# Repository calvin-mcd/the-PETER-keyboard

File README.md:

# the PETER keyboard

compact 60ish keyboard inspired by 40s layouts & formfactors

I designed this keyboard after asking my friend Peter what his ideal keyboard would be. His answer was:"Ehm... I like numbers!". So I tried to make a board that keeps the functionality of a 60% keyboard while offering it in a 40s inspired form factor.

It takes inspiration from ai03’s [UT47.2](https://github.com/ai03-2725/UT47.2) and EODesigns\#4352’s [Humble40](https://geekhack.org/index.php?topic=112927.0) as well as trash man\#6005’s [v4n4g0n](https://trashman.wiki/keyboards/v4n4g0n) and NoahK\#1290’s [Monorail](https://trashman.wiki/community/pcbs/monorail) pcbs.

The case is based on rain\#3950's [mfr2](https://github.com/rainkeebs/mfr2) and has been edited by Gizzle\#9369 to allow for bottom mounting inspired by projectcain\#5265's [vault35](https://mechvault.net/products/vault-35-mini-keyboard)

## Layout

[Link](https://www.keyboard-layout-editor.com/#/gists/bfbfb0e68d74f1cbb328a13727df050d)

## Pictures

## Disclaimer

This project has been tested and confirmed to work. However, no-one involved in this project is responsible for any usage issues that may arise. Order at your own risk. Feel free to edit, modify and otherwise utilise these files.

## License

This project is released under the GPL v3 License. Please refer to the LICENCE file.

## Credits

As always big thanks to the many people who helped me with the pcb, firmware, case design and much more! Escpecially NoahK\#1290, Gizzle\#9369, Iceage\#8817, Dana\#5035, Sierry\#7140 & TweetyDaBird\#3276!

Any questions, contact Calvin\#0563 on Discord.

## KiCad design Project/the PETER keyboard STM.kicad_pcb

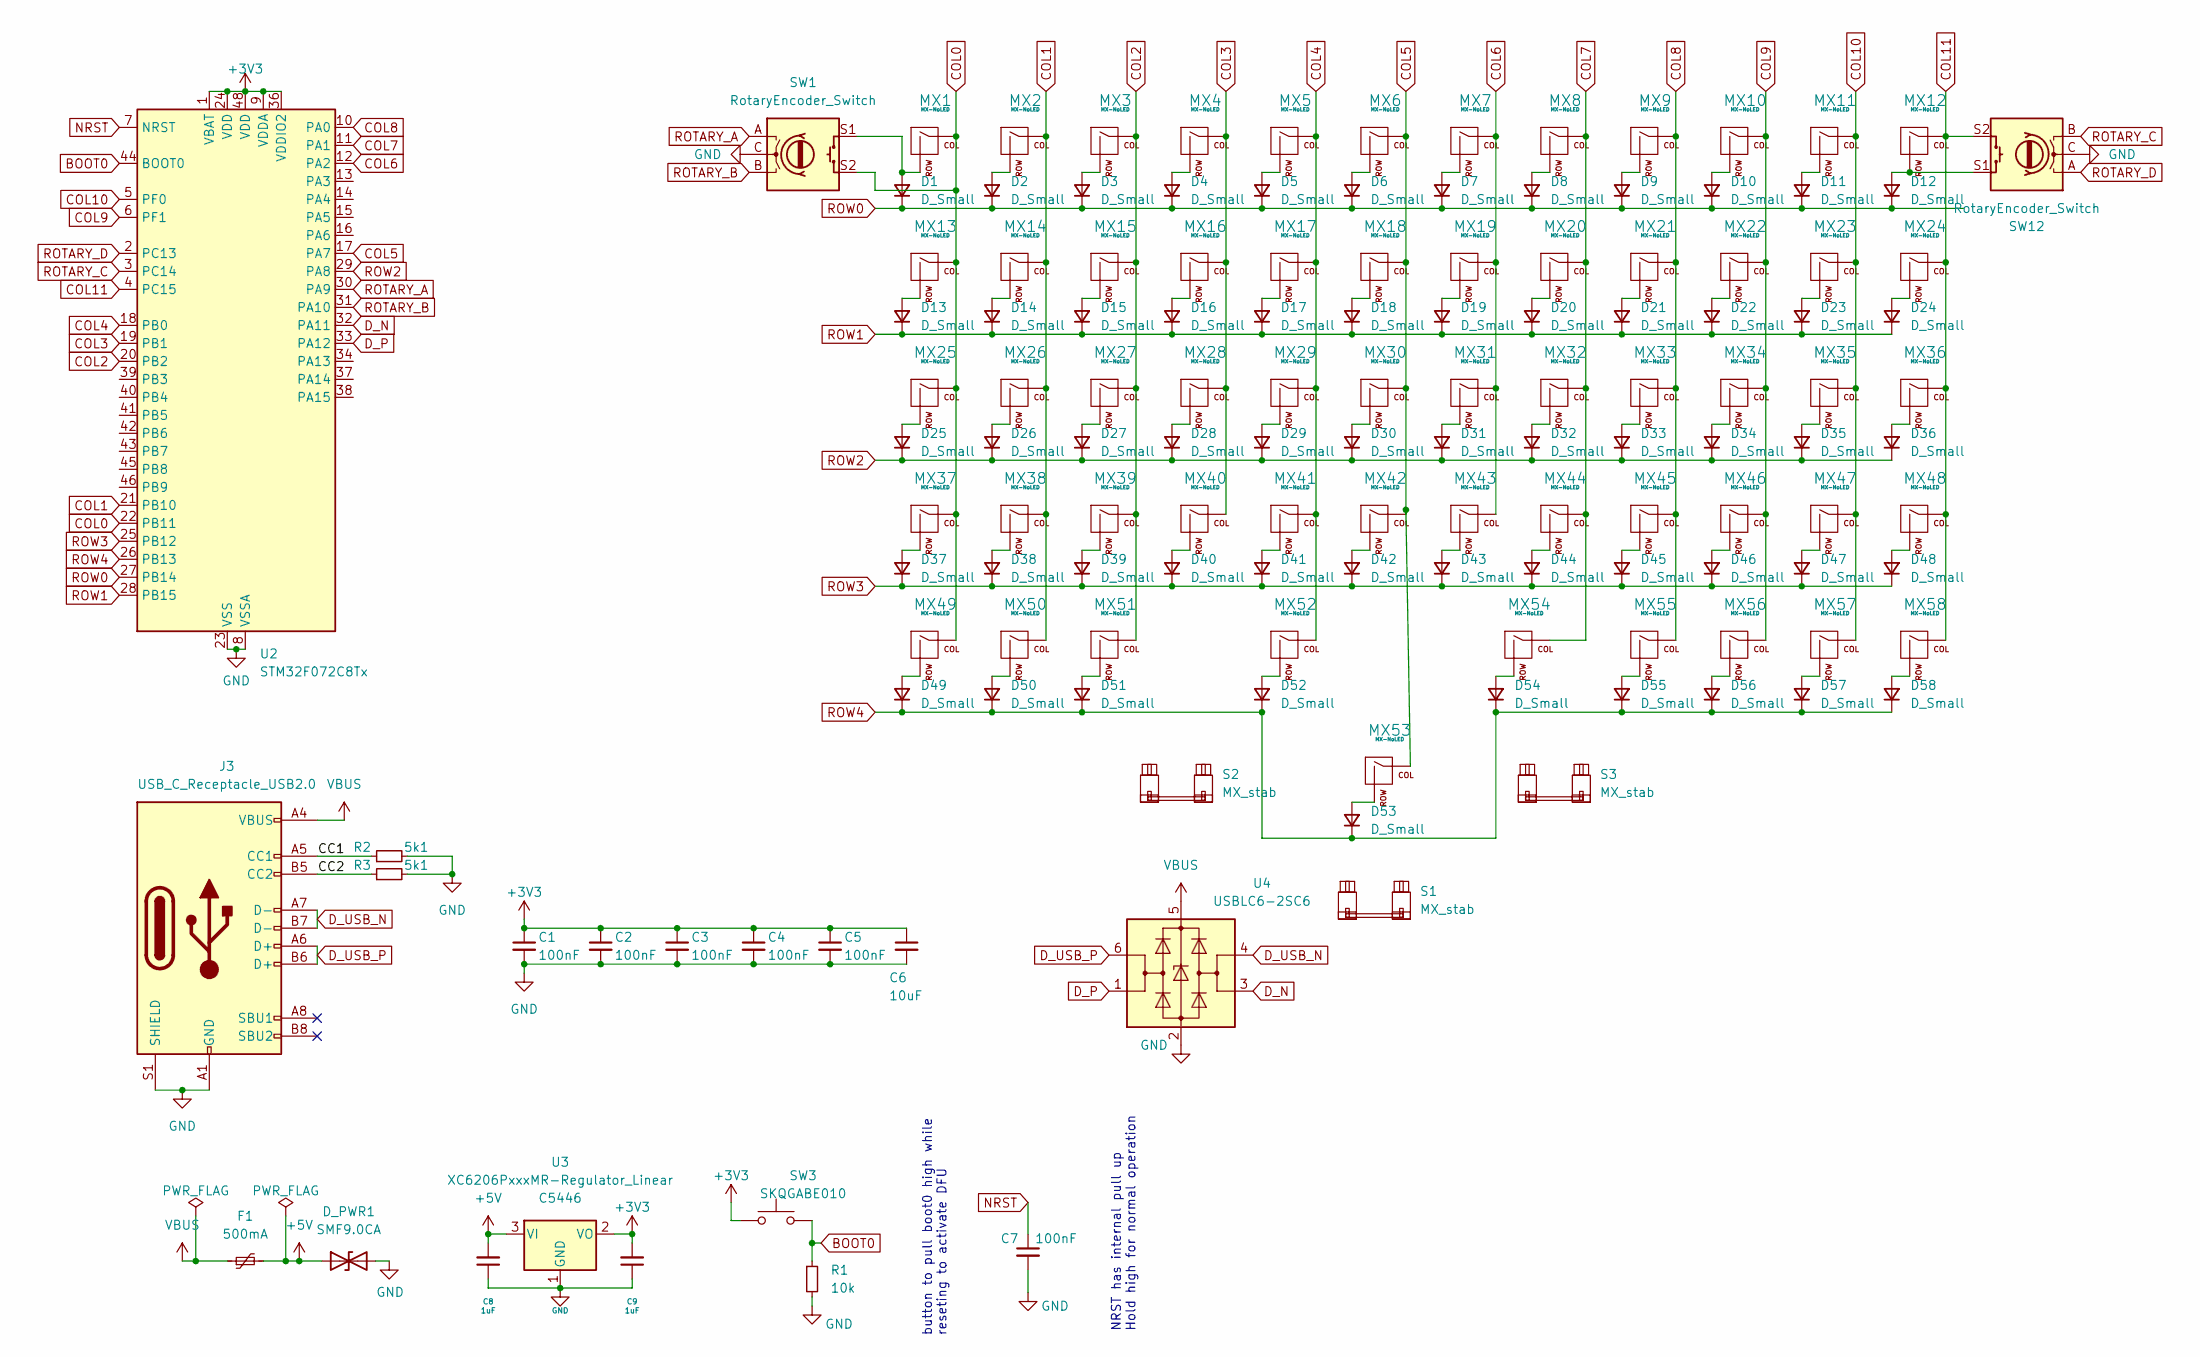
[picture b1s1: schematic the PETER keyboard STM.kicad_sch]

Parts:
C1, C2, C3, C4, C5: 100nF; C_0402_1005Metric
C6: 10uF; C_0402_1005Metric
C7: 100nF; C_0402_1005Metric; LCSC C307331
C8, C9: 1uF; C_0402_1005Metric; LCSC C52923
D1, D2, D3, D4, D5, D6, D7, D8, D9, D10, D11, D12, D13, D14, D15, D16, D17, D18, D19, D20, D21, D22, D23, D24, D25, D26, D27, D28, D29, D30, D31, D32, D33, D34, D35, D36, D37, D38, D39, D40, D41, D42, D43, D44, D45, D46, D47, D48, D49, D50, D51, D52, D53, D54, D55, D56, D57, D58: D_Small; D_SOD-123F
D_PWR1: SMF9.0CA; D_SOD-123
F1: 500mA; Fuse_1206_3216Metric; LCSC C70076
J3: USB_C_Receptacle_USB2.0; USB_C_Receptacle_HRO_TYPE-C-31-M-12; LCSC C165948
MX1, MX2, MX3, MX4, MX5, MX6, MX7, MX8, MX9, MX10, MX11, MX12, MX13, MX14, MX15, MX16, MX17, MX18, MX19, MX20, MX21, MX22, MX23, MX26, MX27, MX28, MX29, MX30, MX31, MX32, MX33, MX34, MX35, MX38, MX39, MX40, MX41, MX42, MX43, MX44, MX45, MX46, MX47, MX48, MX50, MX52, MX53, MX54, MX55, MX56, MX57, MX58: MX-NoLED; SW_MX_HS_S_CPG151101S11_1u
MX24, MX37: MX-NoLED; SW_MX_HS_CPG151101S11_1.5u
MX25, MX36, MX49, MX51: MX-NoLED; SW_MX_HS_CPG151101S11_1.25u
R1: 10k; R_0402_1005Metric
R2, R3: 5k1; R_0402_1005Metric; LCSC C25905
S1: MX_stab; STAB_MX_P_6u
S2: MX_stab; STAB_MX_P_2.25u
S3: MX_stab; STAB_MX_P_2.75u
SW1, SW12: RotaryEncoder_Switch; ROT_Alps_EC11E-Switch
SW3: SKQGABE010; SW_Push_SPST_NO_Alps_SKRK; LCSC C115351
U2: STM32F072C8Tx; LQFP-48_7x7mm_P0.5mm
U3: XC6206PxxxMR-Regulator_Linear; SOT-23; LCSC C5446
U4: USBLC6-2SC6; SOT-23-6; LCSC C2827654

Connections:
+3V3: C1.1, C2.1, C3.1, C4.1, C5.1, C6.1, C9.2, SW3.1, U2.1 (VBAT), U2.9 (VDDA), U2.24 (VDD), U2.36 (VDDIO2), U2.48 (VDD), U3.2 (VO)
+5V: C8.2, D_PWR1.1 (A1), F1.2, U3.3 (VI)
/CC1: J3.A5 (CC1), R2.1
/CC2: J3.B5 (CC2), R3.1
BOOT0: R1.1, SW3.2, U2.44 (BOOT0)
COL0: MX1.1 (COL), MX13.1 (COL), MX25.1 (COL), MX37.1 (COL), MX49.1 (COL), SW1.S2, U2.22 (PB11)
COL1: MX2.1 (COL), MX14.1 (COL), MX26.1 (COL), MX38.1 (COL), MX50.1 (COL), U2.21 (PB10)
COL2: MX3.1 (COL), MX15.1 (COL), MX27.1 (COL), MX39.1 (COL), MX51.1 (COL), U2.20 (PB2)
COL3: MX4.1 (COL), MX16.1 (COL), MX28.1 (COL), MX40.1 (COL), U2.19 (PB1)
COL4: MX5.1 (COL), MX17.1 (COL), MX29.1 (COL), MX41.1 (COL), MX52.1 (COL), U2.18 (PB0)
COL5: MX6.1 (COL), MX18.1 (COL), MX30.1 (COL), MX42.1 (COL), MX53.1 (COL), U2.17 (PA7)
COL6: MX7.1 (COL), MX19.1 (COL), MX31.1 (COL), MX43.1 (COL), U2.12 (PA2)
COL7: MX8.1 (COL), MX20.1 (COL), MX32.1 (COL), MX44.1 (COL), MX54.1 (COL), U2.11 (PA1)
COL8: MX9.1 (COL), MX21.1 (COL), MX33.1 (COL), MX45.1 (COL), MX55.1 (COL), U2.10 (PA0)
COL9: MX10.1 (COL), MX22.1 (COL), MX34.1 (COL), MX46.1 (COL), MX56.1 (COL), U2.6 (PF1)
COL10: MX11.1 (COL), MX23.1 (COL), MX35.1 (COL), MX47.1 (COL), MX57.1 (COL), U2.5 (PF0)
COL11: MX12.1 (COL), MX24.1 (COL), MX36.1 (COL), MX48.1 (COL), MX58.1 (COL), SW12.S2, U2.4 (PC15)
D_N: U2.32 (PA11), U4.3 (I/O2)
D_P: U2.33 (PA12), U4.1 (I/O1)
D_USB_N: J3.A7 (D-), J3.B7 (D-), U4.4 (I/O2)
D_USB_P: J3.A6 (D+), J3.B6 (D+), U4.6 (I/O1)
GND: C1.2, C2.2, C3.2, C4.2, C5.2, C6.2, C7.2, C8.1, C9.1, D_PWR1.2 (A2), J3.A1 (GND), J3.A12 (GND), J3.B1 (GND), J3.B12 (GND), J3.S1 (SHIELD), R1.2, R2.2, R3.2, SW1.C, SW12.C, U2.8 (VSSA), U2.23 (VSS), U2.35 (VSS), U2.47 (VSS), U3.1 (GND), U4.2 (GND)
NRST: C7.1, U2.7 (NRST)
unnamed: D1.2 (A), MX1.2 (ROW), SW1.S1
unnamed: D2.2 (A), MX2.2 (ROW)
unnamed: D3.2 (A), MX3.2 (ROW)
unnamed: D4.2 (A), MX4.2 (ROW)
unnamed: D5.2 (A), MX5.2 (ROW)
unnamed: D6.2 (A), MX6.2 (ROW)
unnamed: D7.2 (A), MX7.2 (ROW)
unnamed: D8.2 (A), MX8.2 (ROW)
unnamed: D9.2 (A), MX9.2 (ROW)
unnamed: D10.2 (A), MX10.2 (ROW)
unnamed: D11.2 (A), MX11.2 (ROW)
unnamed: D12.2 (A), MX12.2 (ROW), SW12.S1
unnamed: D13.2 (A), MX13.2 (ROW)
unnamed: D14.2 (A), MX14.2 (ROW)
unnamed: D15.2 (A), MX15.2 (ROW)
unnamed: D16.2 (A), MX16.2 (ROW)
unnamed: D17.2 (A), MX17.2 (ROW)
unnamed: D18.2 (A), MX18.2 (ROW)
unnamed: D19.2 (A), MX19.2 (ROW)
unnamed: D20.2 (A), MX20.2 (ROW)
unnamed: D21.2 (A), MX21.2 (ROW)
unnamed: D22.2 (A), MX22.2 (ROW)
unnamed: D23.2 (A), MX23.2 (ROW)
unnamed: D24.2 (A), MX24.2 (ROW)
unnamed: D25.2 (A), MX25.2 (ROW)
unnamed: D26.2 (A), MX26.2 (ROW)
unnamed: D27.2 (A), MX27.2 (ROW)
unnamed: D28.2 (A), MX28.2 (ROW)
unnamed: D29.2 (A), MX29.2 (ROW)
unnamed: D30.2 (A), MX30.2 (ROW)
unnamed: D31.2 (A), MX31.2 (ROW)
unnamed: D32.2 (A), MX32.2 (ROW)
unnamed: D33.2 (A), MX33.2 (ROW)
unnamed: D34.2 (A), MX34.2 (ROW)
unnamed: D35.2 (A), MX35.2 (ROW)
unnamed: D36.2 (A), MX36.2 (ROW)
unnamed: D37.2 (A), MX37.2 (ROW)
unnamed: D38.2 (A), MX38.2 (ROW)
unnamed: D39.2 (A), MX39.2 (ROW)
unnamed: D40.2 (A), MX40.2 (ROW)
unnamed: D41.2 (A), MX41.2 (ROW)
unnamed: D42.2 (A), MX42.2 (ROW)
unnamed: D43.2 (A), MX43.2 (ROW)
unnamed: D44.2 (A), MX44.2 (ROW)
unnamed: D45.2 (A), MX45.2 (ROW)
unnamed: D46.2 (A), MX46.2 (ROW)
unnamed: D47.2 (A), MX47.2 (ROW)
unnamed: D48.2 (A), MX48.2 (ROW)
unnamed: D49.2 (A), MX49.2 (ROW)
unnamed: D50.2 (A), MX50.2 (ROW)
unnamed: D51.2 (A), MX51.2 (ROW)
unnamed: D52.2 (A), MX52.2 (ROW)
unnamed: D53.2 (A), MX53.2 (ROW)
unnamed: D54.2 (A), MX54.2 (ROW)
unnamed: D55.2 (A), MX55.2 (ROW)
unnamed: D56.2 (A), MX56.2 (ROW)
unnamed: D57.2 (A), MX57.2 (ROW)
unnamed: D58.2 (A), MX58.2 (ROW)
ROTARY_A: SW1.A, U2.30 (PA9)
ROTARY_B: SW1.B, U2.31 (PA10)
ROTARY_C: SW12.B, U2.3 (PC14)
ROTARY_D: SW12.A, U2.2 (PC13)
ROW0: D1.1 (K), D2.1 (K), D3.1 (K), D4.1 (K), D5.1 (K), D6.1 (K), D7.1 (K), D8.1 (K), D9.1 (K), D10.1 (K), D11.1 (K), D12.1 (K), U2.27 (PB14)
ROW1: D13.1 (K), D14.1 (K), D15.1 (K), D16.1 (K), D17.1 (K), D18.1 (K), D19.1 (K), D20.1 (K), D21.1 (K), D22.1 (K), D23.1 (K), D24.1 (K), U2.28 (PB15)
ROW2: D25.1 (K), D26.1 (K), D27.1 (K), D28.1 (K), D29.1 (K), D30.1 (K), D31.1 (K), D32.1 (K), D33.1 (K), D34.1 (K), D35.1 (K), D36.1 (K), U2.29 (PA8)
ROW3: D37.1 (K), D38.1 (K), D39.1 (K), D40.1 (K), D41.1 (K), D42.1 (K), D43.1 (K), D44.1 (K), D45.1 (K), D46.1 (K), D47.1 (K), D48.1 (K), U2.25 (PB12)
ROW4: D49.1 (K), D50.1 (K), D51.1 (K), D52.1 (K), D53.1 (K), D54.1 (K), D55.1 (K), D56.1 (K), D57.1 (K), D58.1 (K), U2.26 (PB13)
VBUS: F1.1, J3.A4 (VBUS), J3.A9 (VBUS), J3.B4 (VBUS), J3.B9 (VBUS), U4.5 (VBUS)

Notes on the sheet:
button to pull boot0 high while reseting to activate DFU
NRST has internal pull up Hold high for normal operation

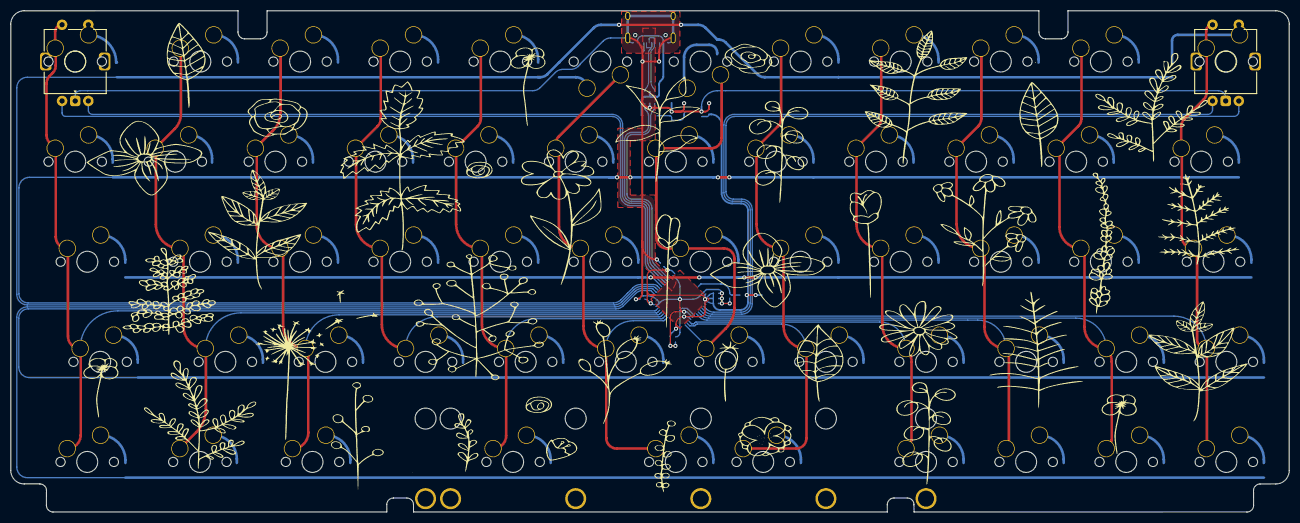
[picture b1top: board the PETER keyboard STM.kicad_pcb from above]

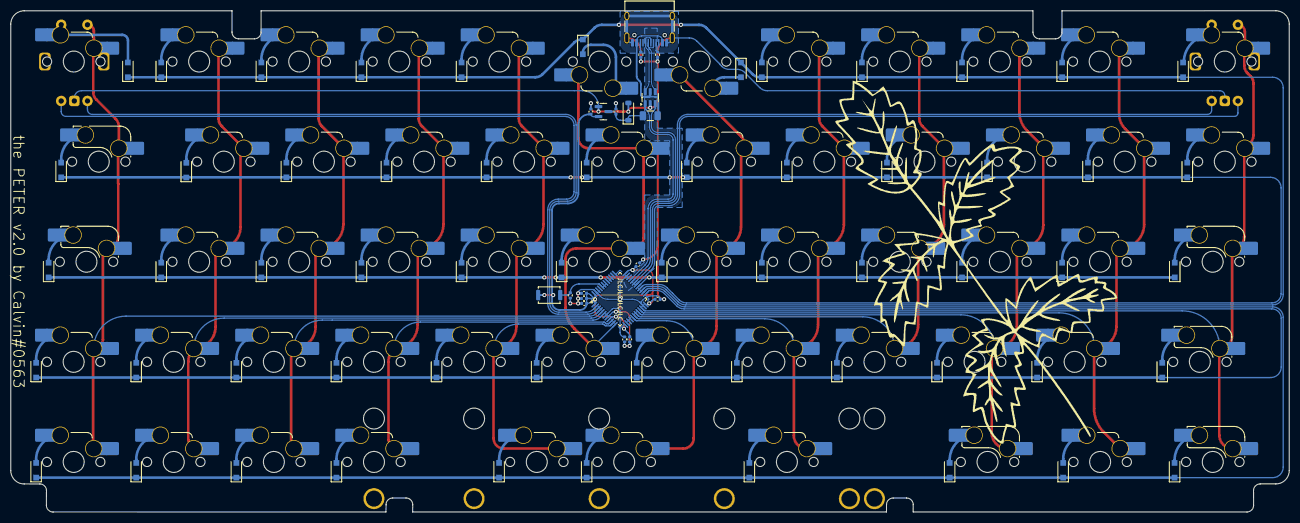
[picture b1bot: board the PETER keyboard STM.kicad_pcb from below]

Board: 2 copper layers, 243.3 x 95.4 mm, 140 parts (135 on the bottom side), 91 nets.

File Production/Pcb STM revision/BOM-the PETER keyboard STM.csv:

Comment,Designator,Footprint,LCSC,Quantity
100nF,"C1,C2,C3,C4,C5,C7",C_0402_1005Metric,C307331,6
10k,R1,R_0402_1005Metric,C25744,1
10uF,C6,C_0402_1005Metric,C15525,1
1uF,"C8,C9",C_0402_1005Metric,C52923,2
500mA,F1,Fuse_1206_3216Metric,C70076,1
5k1,"R2,R3",R_0402_1005Metric,C25905,2
D_Small,"D1,D10,D11,D12,D13,D14,D15,D16,D17,D18,D19,D2,D20,D21,D22,D23,D24,D25,D26,D27,D28,D29,D3,D30,D31,D32,D33,D34,D35,D36,D37,D38,D39,D4,D40,D41,D42,D43,D44,D45,D46,D47,D48,D49,D5,D50,D51,D52,D53,D54,D55,D56,D57,D58,D6,D7,D8,D9",D_SOD-123F,C64898,58
SKQGABE010,SW3,SW_Push_SPST_NO_Alps_SKRK,C115357,1
SMF9.0CA,D_PWR1,D_SOD-123,C707469,1
STM32F072C8Tx,U2,LQFP-48_7x7mm_P0.5mm,C81720,1
USBLC6-2SC6,U4,SOT-23-6,C2827654,1
USB_C_Receptacle_USB2.0,J3,USB_C_Receptacle_HRO_TYPE-C-31-M-12,C165948,1
XC6206PxxxMR-Regulator_Linear,U3,SOT-23,C5446,1

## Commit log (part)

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2022-09-26 Setting up the project
2022-09-26 Add submodules
2022-09-26 setting up libraries
2022-09-26 MCU set up
    MCU and USB set up
2022-09-26 starting to set up matrix
2022-09-26 switch matrix set up complete
    whole switch matrix,
    but no rotary encoders yet,
    no usb c
2022-09-26 schematics for USB C added
    shielding not complete
2022-09-26 added first draft of rotary encoders
    not confirmed to work
2022-09-26 USB c cleaned up
    older USB port removed
2022-09-26 footprints assigned to schematics
2022-09-27 PCB editor
    placing switch matrix
2022-09-27 Switches and Diodes placed, margins assigned
    still need to figure out placement of usb, and MCU
2022-09-27 matrix tracing
2022-09-27 starting mcu traces
2022-09-27 reworked DSM placement, exchanged MCU for smaller
2022-09-28 trying to trace mcu, usb
    no success yet
2022-09-28 more attempts at changing mcu
2022-09-29 placed MCU and USB for automatic routing
    also assigned row and col to MCU
2022-09-30 traces have been auto routed
2022-09-30 re doing the auto routing
    having to start again
2022-09-30 back to autorouting
2022-09-30 moving MCU around, no trace attempt yet
2022-09-30 just checking in on the files
2022-10-01 just tried and deleted a silkscreen
2022-10-02 reworking pcb placement according to schematics
2022-10-02 manual routing
2022-10-03 traces added for rows and columns
    rotary encoders are still left
2022-10-03 all tracing done, curves applied
2022-10-04 starting to redo mcu and usb
2022-10-05 setting up changes
2022-10-05 still trying to set correct tolerances!
2022-10-06 more routing work
2022-10-07 cleaned up MCU, USB. Connected rows. Assigned to MCU. now routing rows & cols
2022-10-07 all traces routed
    no curves, no grounding routes drawn
2022-10-07 again all routes drawn
    no curves, no GND
2022-10-07 routes and curves
    no GND
2022-10-07 first silkscreen implementation
2022-10-08 silkscreens added
2022-10-08 created a switchplate
2022-10-08 switchplate clean up
2022-10-09 created gerbers, added front silkscreen, cleaned up folder
2022-10-09 generate gerber for plate file
2022-10-11 planning m2 holes and relief cuts
2022-10-11 planning out m2 and relief cuts
2022-10-15 backup update
2022-10-20 added hotswap and mounting holes for reference
    need to add cuts to pcb, reroute matrix and usb, mcu
2022-10-21 about to reroute the whole damn thing!
2022-10-21 rerouting
2022-10-21 rerouting
    routed matrix, MCU, USB, rotary encoders still to do
2022-10-22 rerouting, plate cuts
    rerouted mcu, usb, all rows and cols. added plate cuts for bottom mounting
2022-10-22 routing done
    all routing done, curves added. 6u swapped for hotswap again. STABILIZERS NOT CHANGED YET
2022-10-22 cleaned pcb, cleaned switchplate
2022-10-22 deleted unnecessary files
2022-10-22 pcb, plate cleaned
    stabs reversed
2022-10-23 ignore library
    was unnecessary
2022-10-25 gnd fill changed, bottom mounting changed
    switchplate has not been adapted, routing not working
2022-10-25 edgecut pcb updated, switchplate updated
2022-10-25 changes to pcb, plate, DRC cleanup
2022-10-25 created production files for all parts
    parts list still missing
2022-10-26 created BOM, POS, production files for JLC
2022-10-27 changing silkscreen to fit edge cuts
    for production files
2022-10-27 adapting gerbers
2022-10-27 production updated
2022-10-29 generating fresh POM&POS files for production
2022-11-08 production files organised
2022-11-10 updated BOM with correct crystal
2022-11-10 BOM updated
2022-11-10 BOM update
2022-11-26 completing project, cleaning folders
2022-12-12 create production zip
2022-12-17 clean up
2022-12-22 insecure vial
2022-12-22 added image folder
2022-12-27 exported switchplate
2022-12-27 trying to export plate
2022-12-31 added case file
2023-01-02 updated case file
2023-01-09 cleaned up schematics
2023-01-10 readme update
2023-01-10 updated readme, made public
2023-01-11 added keymap
2023-01-15 backup
2023-01-21 auto save
2023-01-22 accessing production files for reference
2023-03-10 small clean up
2023-05-29 updated BOM with correct parts
2023-08-20 added image of peter's PETER
2025-03-01 revision wip
2026-03-24 stm revision
2026-04-05 production files STM
2026-04-19 kicad 9
    gnd zones
